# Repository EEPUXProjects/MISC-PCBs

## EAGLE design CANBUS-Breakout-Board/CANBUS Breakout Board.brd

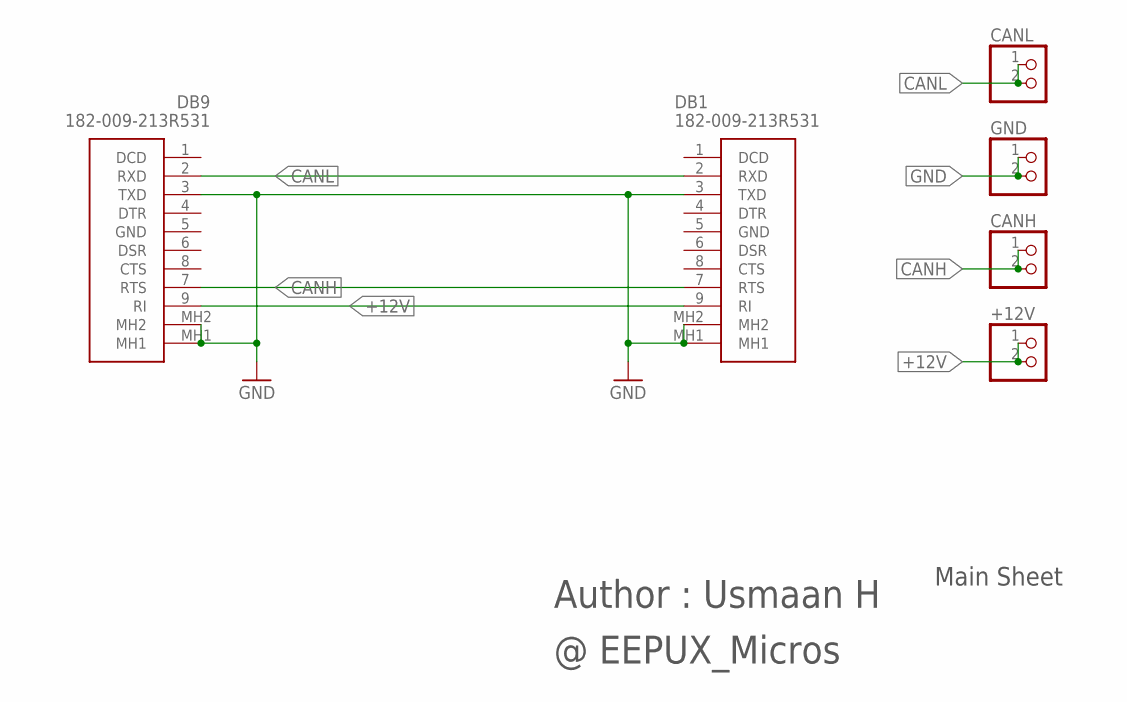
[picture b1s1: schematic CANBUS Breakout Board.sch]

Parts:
+12V: PINHD-1X2; 1X02
CANH: PINHD-1X2; 1X02
CANL: PINHD-1X2; 1X02
DB1, DB9: 182-009-213R531; 182009213R531
GND: PINHD-1X2; 1X02

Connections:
+12V: +12V.1, +12V.2, DB1.9 (RI), DB9.9 (RI)
CANH: CANH.1, CANH.2, DB1.7 (RTS), DB9.7 (RTS)
CANL: CANL.1, CANL.2, DB1.2 (RXD), DB9.2 (RXD)
GND: DB1.3 (TXD), DB1.MH1, DB1.MH2, DB9.3 (TXD), DB9.MH1, DB9.MH2, GND.1, GND.2

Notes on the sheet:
Author : Usmaan H
@ EEPUX_Micros
Main Sheet

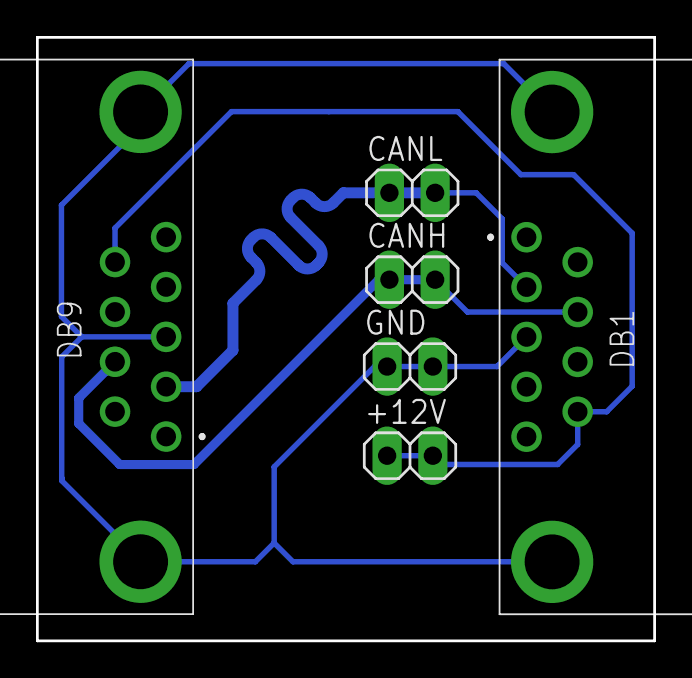
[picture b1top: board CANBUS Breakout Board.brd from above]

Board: 2 copper layers, 34.3 x 33.5 mm, 6 parts (0 on the bottom side), 4 nets.

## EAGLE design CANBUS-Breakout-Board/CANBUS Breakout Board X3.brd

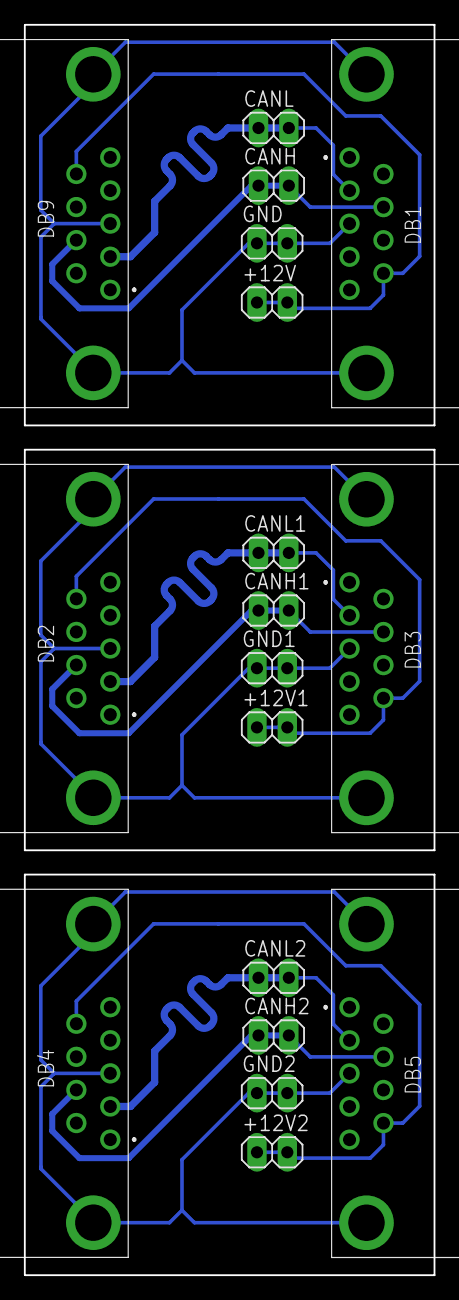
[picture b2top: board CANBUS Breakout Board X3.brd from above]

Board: 2 copper layers, 34.3 x 104.6 mm, 18 parts (0 on the bottom side), 12 nets.

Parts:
+12V, +12V1, +12V2: 1X02
CANH, CANH1, CANH2: 1X02
CANL, CANL1, CANL2: 1X02
DB1, DB2, DB3, DB4, DB5, DB9: 182-009-213R531; 182009213R531
GND, GND1, GND2: 1X02

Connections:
+12V: +12V.1, +12V.2, DB1.9, DB9.9
+12V1: +12V1.1, +12V1.2, DB2.9, DB3.9
+12V2: +12V2.1, +12V2.2, DB4.9, DB5.9
CANH: CANH.1, CANH.2, DB1.7, DB9.7
CANH1: CANH1.1, CANH1.2, DB2.7, DB3.7
CANH2: CANH2.1, CANH2.2, DB4.7, DB5.7
CANL: CANL.1, CANL.2, DB1.2, DB9.2
CANL1: CANL1.1, CANL1.2, DB2.2, DB3.2
CANL2: CANL2.1, CANL2.2, DB4.2, DB5.2
GND: DB1.3, DB1.MH1, DB1.MH2, DB9.3, DB9.MH1, DB9.MH2, GND.1, GND.2
GND1: DB2.3, DB2.MH1, DB2.MH2, DB3.3, DB3.MH1, DB3.MH2, GND1.1, GND1.2
GND2: DB4.3, DB4.MH1, DB4.MH2, DB5.3, DB5.MH1, DB5.MH2, GND2.1, GND2.2

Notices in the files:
parts and their libraries:
SparkFun-Aesthetics: Licensing: CC v3.0 Share-Alike You are welcome to use this library for commercial purposes.
